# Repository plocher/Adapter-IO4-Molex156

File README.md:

# Adapter-IO4-Molex156
## License: CERN Open Hardware Licence v1.2

RJ12/6 breakout board, for 0.156 (molex) connector or direct wire soldering

IO4 0.156" Breakout board

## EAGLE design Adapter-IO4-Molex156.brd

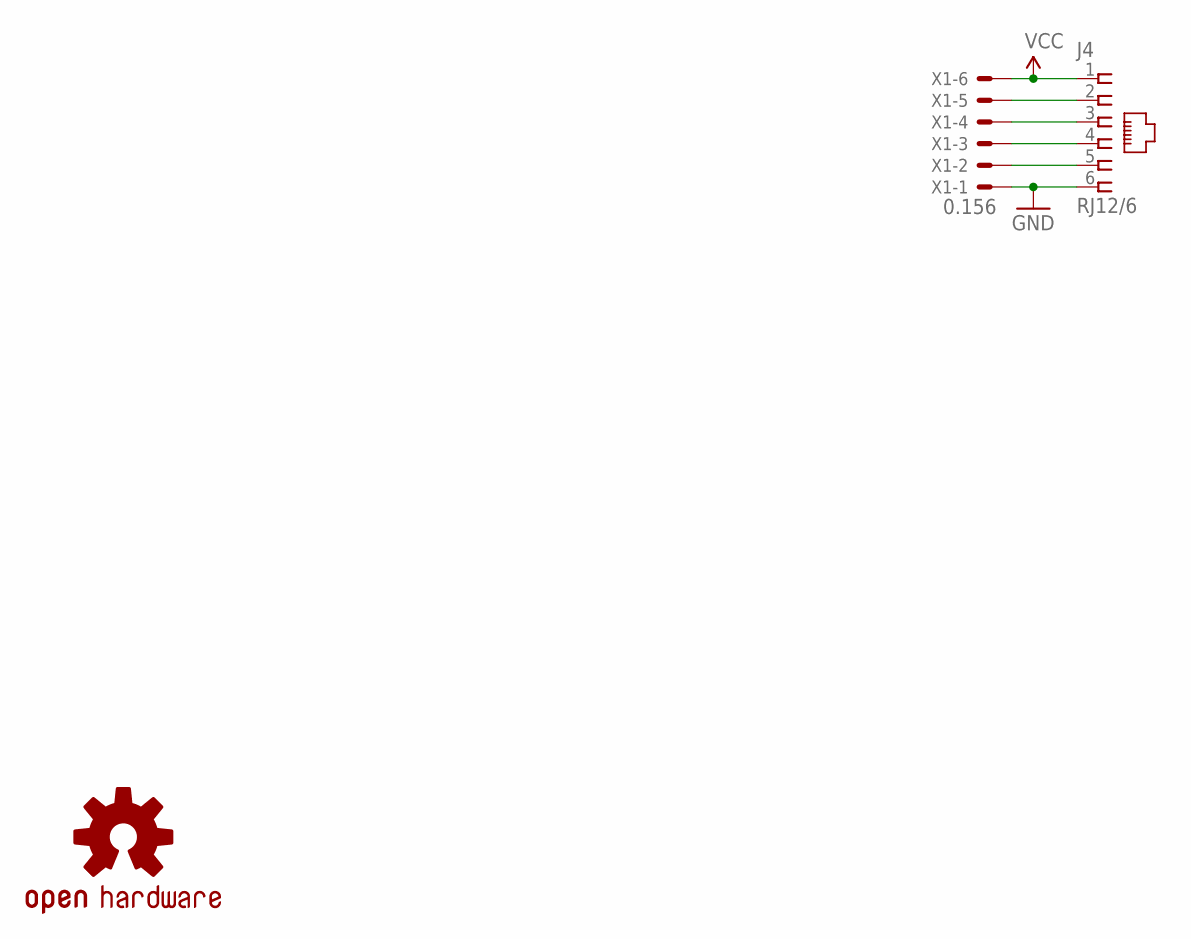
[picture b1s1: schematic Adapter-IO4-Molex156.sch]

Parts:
J4: RJ12/6; RJ25-PANEL
U$1: OSHW; OSHW-LOGO-M
X1: 0.156; KK-156-6

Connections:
GND: J4.6, X1.1
IO1: J4.2, X1.5
IO2: J4.3, X1.4
IO3: J4.4, X1.3
IO4: J4.5, X1.2
VCC: J4.1, X1.6

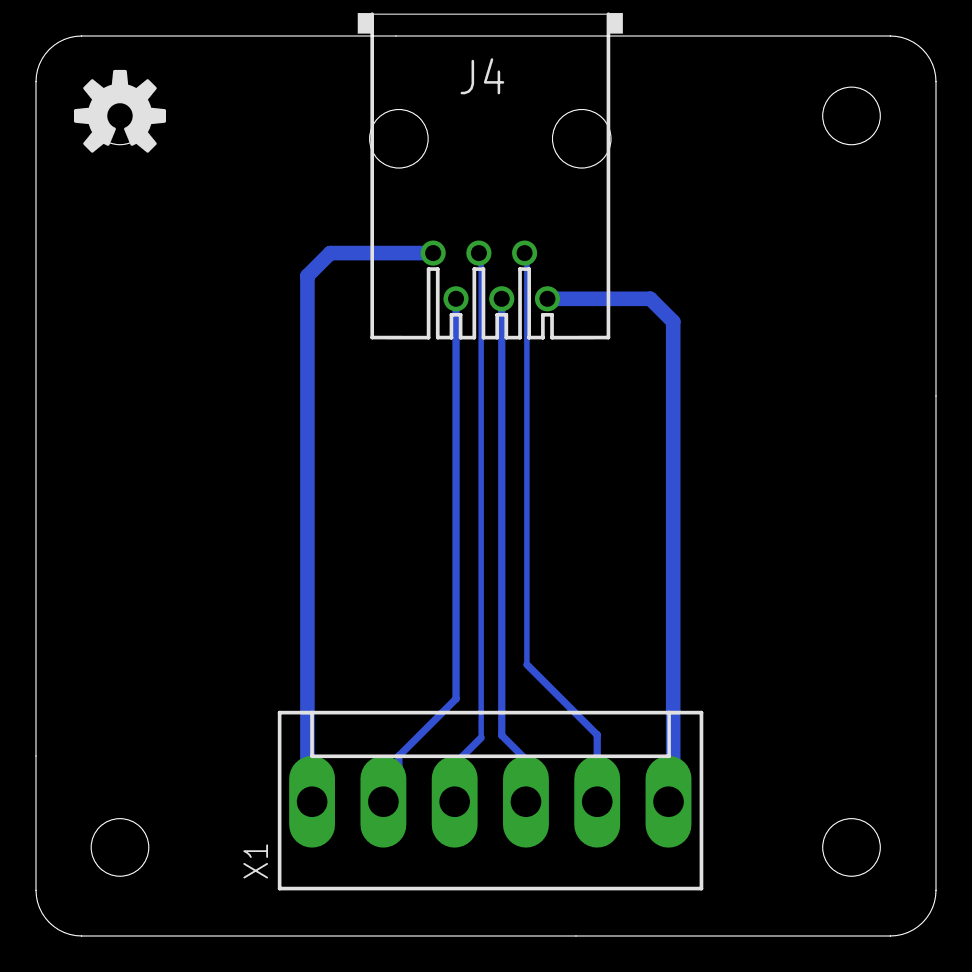
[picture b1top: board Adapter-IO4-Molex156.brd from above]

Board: 2 copper layers, 50.0 x 50.0 mm, 3 parts (0 on the bottom side), 6 nets.

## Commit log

2019-12-09 added graphic
2020-05-04 updated tags
2020-10-05 added values for connectors
2020-10-06 normalized values

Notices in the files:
parts and their libraries:
SparkFun-Aesthetics: Licensing: CC v3.0 Share-Alike You are welcome to use this library for commercial purposes.
SPCoast: http://freedomdefined.org/OSHW Creative Commons - Attribution - ShareAlike 3.0
